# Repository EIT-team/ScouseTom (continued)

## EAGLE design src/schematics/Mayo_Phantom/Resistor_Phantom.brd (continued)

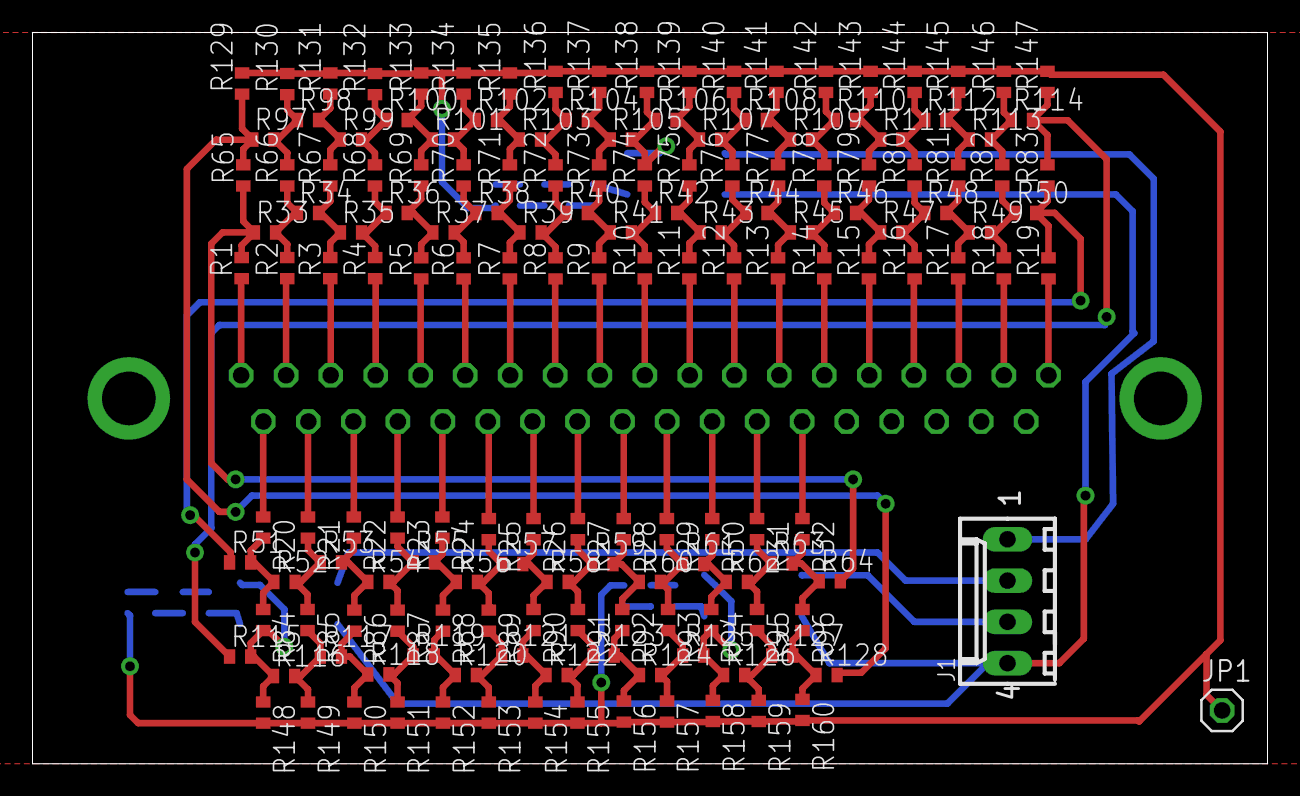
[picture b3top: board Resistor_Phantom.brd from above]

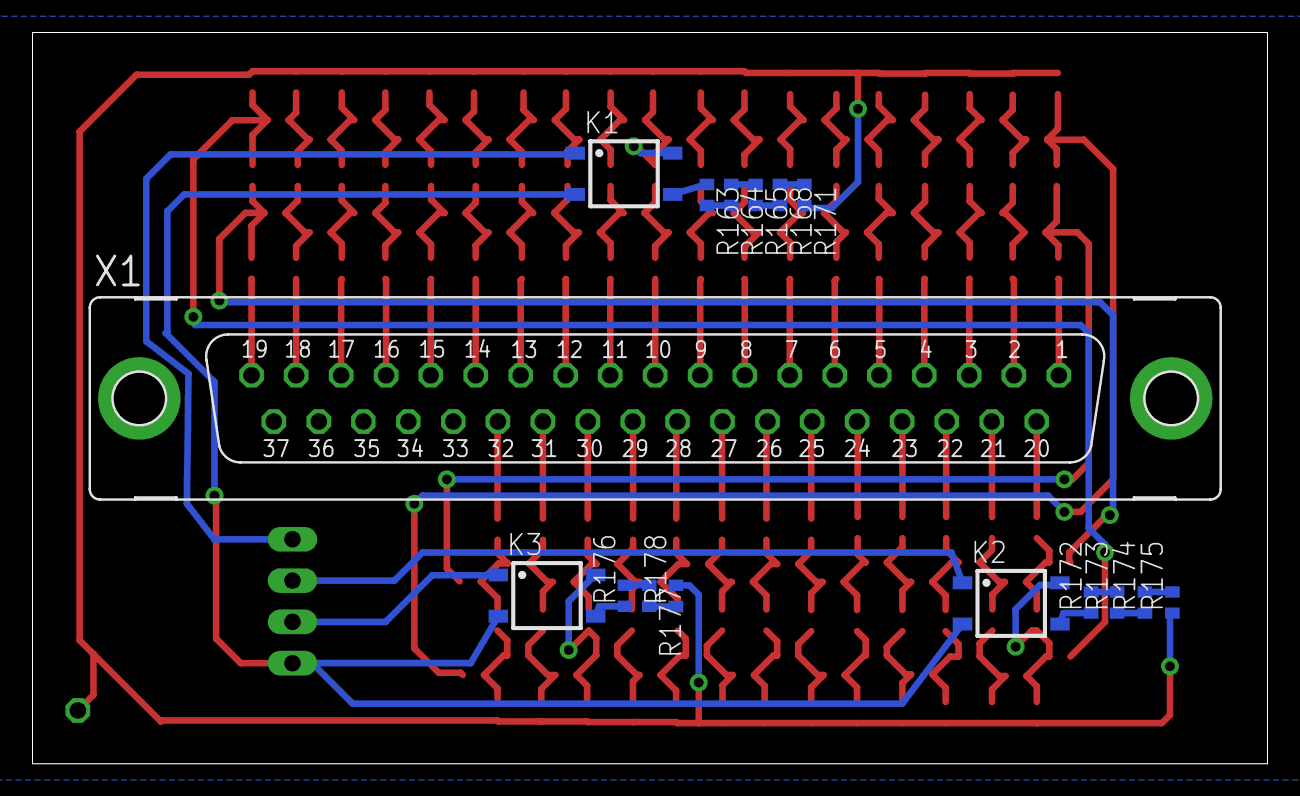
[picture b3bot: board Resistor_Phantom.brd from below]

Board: 2 copper layers, 76.0 x 45.0 mm, 178 parts (16 on the bottom side), 113 nets.

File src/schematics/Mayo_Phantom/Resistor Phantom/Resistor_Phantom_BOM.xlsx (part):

Part | Value | Device | Package | Description | MPN | OC_FARNELL | PCBTRAINFREE
K1 | AQY221R2S | AQY221R2S | SOP04 | PHOTOMOS Relay RF (Radio Frequency) NAiS | AQY221R2S | 1653770
K2 | AQY221R2S | AQY221R2S | SOP04 | PHOTOMOS Relay RF (Radio Frequency) NAiS | AQY221R2S | 1653770
K3 | AQY221R2S | AQY221R2S | SOP04 | PHOTOMOS Relay RF (Radio Frequency) NAiS | AQY221R2S | 1653770
R1 | 1k | R-EU_R0402 | R0402 | RESISTOR, European symbol | MC00625W040211K | 1358043 | PCBTRAINFREESTOCK
R2 | 1k | R-EU_R0402 | R0402 | RESISTOR, European symbol | MC00625W040211K | 1358043 | PCBTRAINFREESTOCK
R3 | 1k | R-EU_R0402 | R0402 | RESISTOR, European symbol | MC00625W040211K | 1358043 | PCBTRAINFREESTOCK
R4 | 1k | R-EU_R0402 | R0402 | RESISTOR, European symbol | MC00625W040211K | 1358043 | PCBTRAINFREESTOCK
R5 | 1k | R-EU_R0402 | R0402 | RESISTOR, European symbol | MC00625W040211K | 1358043 | PCBTRAINFREESTOCK
R6 | 1k | R-EU_R0402 | R0402 | RESISTOR, European symbol | MC00625W040211K | 1358043 | PCBTRAINFREESTOCK
R7 | 1k | R-EU_R0402 | R0402 | RESISTOR, European symbol | MC00625W040211K | 1358043 | PCBTRAINFREESTOCK
R8 | 1k | R-EU_R0402 | R0402 | RESISTOR, European symbol | MC00625W040211K | 1358043 | PCBTRAINFREESTOCK
R9 | 1k | R-EU_R0402 | R0402 | RESISTOR, European symbol | MC00625W040211K | 1358043 | PCBTRAINFREESTOCK
R10 | 1k | R-EU_R0402 | R0402 | RESISTOR, European symbol | MC00625W040211K | 1358043 | PCBTRAINFREESTOCK
R11 | 1k | R-EU_R0402 | R0402 | RESISTOR, European symbol | MC00625W040211K | 1358043 | PCBTRAINFREESTOCK
R12 | 1k | R-EU_R0402 | R0402 | RESISTOR, European symbol | MC00625W040211K | 1358043 | PCBTRAINFREESTOCK
R13 | 1k | R-EU_R0402 | R0402 | RESISTOR, European symbol | MC00625W040211K | 1358043 | PCBTRAINFREESTOCK
R14 | 1k | R-EU_R0402 | R0402 | RESISTOR, European symbol | MC00625W040211K | 1358043 | PCBTRAINFREESTOCK
R15 | 1k | R-EU_R0402 | R0402 | RESISTOR, European symbol | MC00625W040211K | 1358043 | PCBTRAINFREESTOCK
R16 | 1k | R-EU_R0402 | R0402 | RESISTOR, European symbol | MC00625W040211K | 1358043 | PCBTRAINFREESTOCK
R17 | 1k | R-EU_R0402 | R0402 | RESISTOR, European symbol | MC00625W040211K | 1358043 | PCBTRAINFREESTOCK
R18 | 1k | R-EU_R0402 | R0402 | RESISTOR, European symbol | MC00625W040211K | 1358043 | PCBTRAINFREESTOCK
R19 | 1k | R-EU_R0402 | R0402 | RESISTOR, European symbol | MC00625W040211K | 1358043 | PCBTRAINFREESTOCK
R20 | 1k | R-EU_R0402 | R0402 | RESISTOR, European symbol | MC00625W040211K | 1358043 | PCBTRAINFREESTOCK
R21 | 1k | R-EU_R0402 | R0402 | RESISTOR, European symbol | MC00625W040211K | 1358043 | PCBTRAINFREESTOCK
R22 | 1k | R-EU_R0402 | R0402 | RESISTOR, European symbol | MC00625W040211K | 1358043 | PCBTRAINFREESTOCK
R23 | 1k | R-EU_R0402 | R0402 | RESISTOR, European symbol | MC00625W040211K | 1358043 | PCBTRAINFREESTOCK
R24 | 1k | R-EU_R0402 | R0402 | RESISTOR, European symbol | MC00625W040211K | 1358043 | PCBTRAINFREESTOCK
R25 | 1k | R-EU_R0402 | R0402 | RESISTOR, European symbol | MC00625W040211K | 1358043 | PCBTRAINFREESTOCK
R26 | 1k | R-EU_R0402 | R0402 | RESISTOR, European symbol | MC00625W040211K | 1358043 | PCBTRAINFREESTOCK
R27 | 1k | R-EU_R0402 | R0402 | RESISTOR, European symbol | MC00625W040211K | 1358043 | PCBTRAINFREESTOCK
R28 | 1k | R-EU_R0402 | R0402 | RESISTOR, European symbol | MC00625W040211K | 1358043 | PCBTRAINFREESTOCK
R29 | 1k | R-EU_R0402 | R0402 | RESISTOR, European symbol | MC00625W040211K | 1358043 | PCBTRAINFREESTOCK
R30 | 1k | R-EU_R0402 | R0402 | RESISTOR, European symbol | MC00625W040211K | 1358043 | PCBTRAINFREESTOCK
R31 | 1k | R-EU_R0402 | R0402 | RESISTOR, European symbol | MC00625W040211K | 1358043 | PCBTRAINFREESTOCK
R32 | 1k | R-EU_R0402 | R0402 | RESISTOR, European symbol | MC00625W040211K | 1358043 | PCBTRAINFREESTOCK
R33 | 1k | R-EU_R0402 | R0402 | RESISTOR, European symbol | MC00625W040211K | 1358043 | PCBTRAINFREESTOCK
R34 | 1k | R-EU_R0402 | R0402 | RESISTOR, European symbol | MC00625W040211K | 1358043 | PCBTRAINFREESTOCK
R35 | 1k | R-EU_R0402 | R0402 | RESISTOR, European symbol | MC00625W040211K | 1358043 | PCBTRAINFREESTOCK
R36 | 1k | R-EU_R0402 | R0402 | RESISTOR, European symbol | MC00625W040211K | 1358043 | PCBTRAINFREESTOCK
R37 | 1k | R-EU_R0402 | R0402 | RESISTOR, European symbol | MC00625W040211K | 1358043 | PCBTRAINFREESTOCK
R38 | 1k | R-EU_R0402 | R0402 | RESISTOR, European symbol | MC00625W040211K | 1358043 | PCBTRAINFREESTOCK
R39 | 1k | R-EU_R0402 | R0402 | RESISTOR, European symbol | MC00625W040211K | 1358043 | PCBTRAINFREESTOCK
R40 | 1k | R-EU_R0402 | R0402 | RESISTOR, European symbol | MC00625W040211K | 1358043 | PCBTRAINFREESTOCK
R41 | 1k | R-EU_R0402 | R0402 | RESISTOR, European symbol | MC00625W040211K | 1358043 | PCBTRAINFREESTOCK
R42 | 1k | R-EU_R0402 | R0402 | RESISTOR, European symbol | MC00625W040211K | 1358043 | PCBTRAINFREESTOCK
R43 | 1k | R-EU_R0402 | R0402 | RESISTOR, European symbol | MC00625W040211K | 1358043 | PCBTRAINFREESTOCK
R44 | 1k | R-EU_R0402 | R0402 | RESISTOR, European symbol | MC00625W040211K | 1358043 | PCBTRAINFREESTOCK
R45 | 1k | R-EU_R0402 | R0402 | RESISTOR, European symbol | MC00625W040211K | 1358043 | PCBTRAINFREESTOCK
R46 | 1k | R-EU_R0402 | R0402 | RESISTOR, European symbol | MC00625W040211K | 1358043 | PCBTRAINFREESTOCK
R47 | 1k | R-EU_R0402 | R0402 | RESISTOR, European symbol | MC00625W040211K | 1358043 | PCBTRAINFREESTOCK
R48 | 1k | R-EU_R0402 | R0402 | RESISTOR, European symbol | MC00625W040211K | 1358043 | PCBTRAINFREESTOCK
R49 | 1k | R-EU_R0402 | R0402 | RESISTOR, European symbol | MC00625W040211K | 1358043 | PCBTRAINFREESTOCK
R50 | 1k | R-EU_R0402 | R0402 | RESISTOR, European symbol | MC00625W040211K | 1358043 | PCBTRAINFREESTOCK
R51 | 1k | R-EU_R0402 | R0402 | RESISTOR, European symbol | MC00625W040211K | 1358043 | PCBTRAINFREESTOCK
R52 | 1k | R-EU_R0402 | R0402 | RESISTOR, European symbol | MC00625W040211K | 1358043 | PCBTRAINFREESTOCK
R53 | 1k | R-EU_R0402 | R0402 | RESISTOR, European symbol | MC00625W040211K | 1358043 | PCBTRAINFREESTOCK
R54 | 1k | R-EU_R0402 | R0402 | RESISTOR, European symbol | MC00625W040211K | 1358043 | PCBTRAINFREESTOCK
R55 | 1k | R-EU_R0402 | R0402 | RESISTOR, European symbol | MC00625W040211K | 1358043 | PCBTRAINFREESTOCK
R56 | 1k | R-EU_R0402 | R0402 | RESISTOR, European symbol | MC00625W040211K | 1358043 | PCBTRAINFREESTOCK
R57 | 1k | R-EU_R0402 | R0402 | RESISTOR, European symbol | MC00625W040211K | 1358043 | PCBTRAINFREESTOCK
R58 | 1k | R-EU_R0402 | R0402 | RESISTOR, European symbol | MC00625W040211K | 1358043 | PCBTRAINFREESTOCK
R59 | 1k | R-EU_R0402 | R0402 | RESISTOR, European symbol | MC00625W040211K | 1358043 | PCBTRAINFREESTOCK
R60 | 1k | R-EU_R0402 | R0402 | RESISTOR, European symbol | MC00625W040211K | 1358043 | PCBTRAINFREESTOCK
R61 | 1k | R-EU_R0402 | R0402 | RESISTOR, European symbol | MC00625W040211K | 1358043 | PCBTRAINFREESTOCK
R62 | 1k | R-EU_R0402 | R0402 | RESISTOR, European symbol | MC00625W040211K | 1358043 | PCBTRAINFREESTOCK
R63 | 1k | R-EU_R0402 | R0402 | RESISTOR, European symbol | MC00625W040211K | 1358043 | PCBTRAINFREESTOCK
R64 | 1k | R-EU_R0402 | R0402 | RESISTOR, European symbol | MC00625W040211K | 1358043 | PCBTRAINFREESTOCK
R65 | 3k | R-EU_R0402 | R0402 | RESISTOR, European symbol | MC00625W040213K | 2130389 | PCBTRAINFREESTOCK
R66 | 3k | R-EU_R0402 | R0402 | RESISTOR, European symbol | MC00625W040213K | 2130389 | PCBTRAINFREESTOCK
R67 | 3k | R-EU_R0402 | R0402 | RESISTOR, European symbol | MC00625W040213K | 2130389 | PCBTRAINFREESTOCK
R68 | 3k | R-EU_R0402 | R0402 | RESISTOR, European symbol | MC00625W040213K | 2130389 | PCBTRAINFREESTOCK
R69 | 3k | R-EU_R0402 | R0402 | RESISTOR, European symbol | MC00625W040213K | 2130389 | PCBTRAINFREESTOCK
R70 | 3k | R-EU_R0402 | R0402 | RESISTOR, European symbol | MC00625W040213K | 2130389 | PCBTRAINFREESTOCK
R71 | 3k | R-EU_R0402 | R0402 | RESISTOR, European symbol | MC00625W040213K | 2130389 | PCBTRAINFREESTOCK
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
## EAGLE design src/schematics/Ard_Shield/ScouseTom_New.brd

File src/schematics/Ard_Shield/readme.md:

# Arduino Shield

The Arduino Shield has several functions:

- Communication with PC via USB serial. This is done through the programming port on the Arduinio Due. i.e. `Serial.print` etc. with baud rate 115200
- Communication with Keithley 6221 current source via isolated RS232 port - baud rate 57600 via Serial port `Serial1.print` etc.
- Reference triggers to EEG system. Pulses sent to digital inputs of EEG systems, isolated from Arduino pins
- Control of switch networks. Control signals sent to Switchboard (isolation on the switchboard)
- Stimulation triggers - Based on phase marker of Keithley 6221 - stimulation pulses are randomised with respect to the phase of the injected current.
- Stimulation voltage - the voltage of the pulses can be sent from 3.3 to 12 V. This is useful for controlling the electrical stimulator box

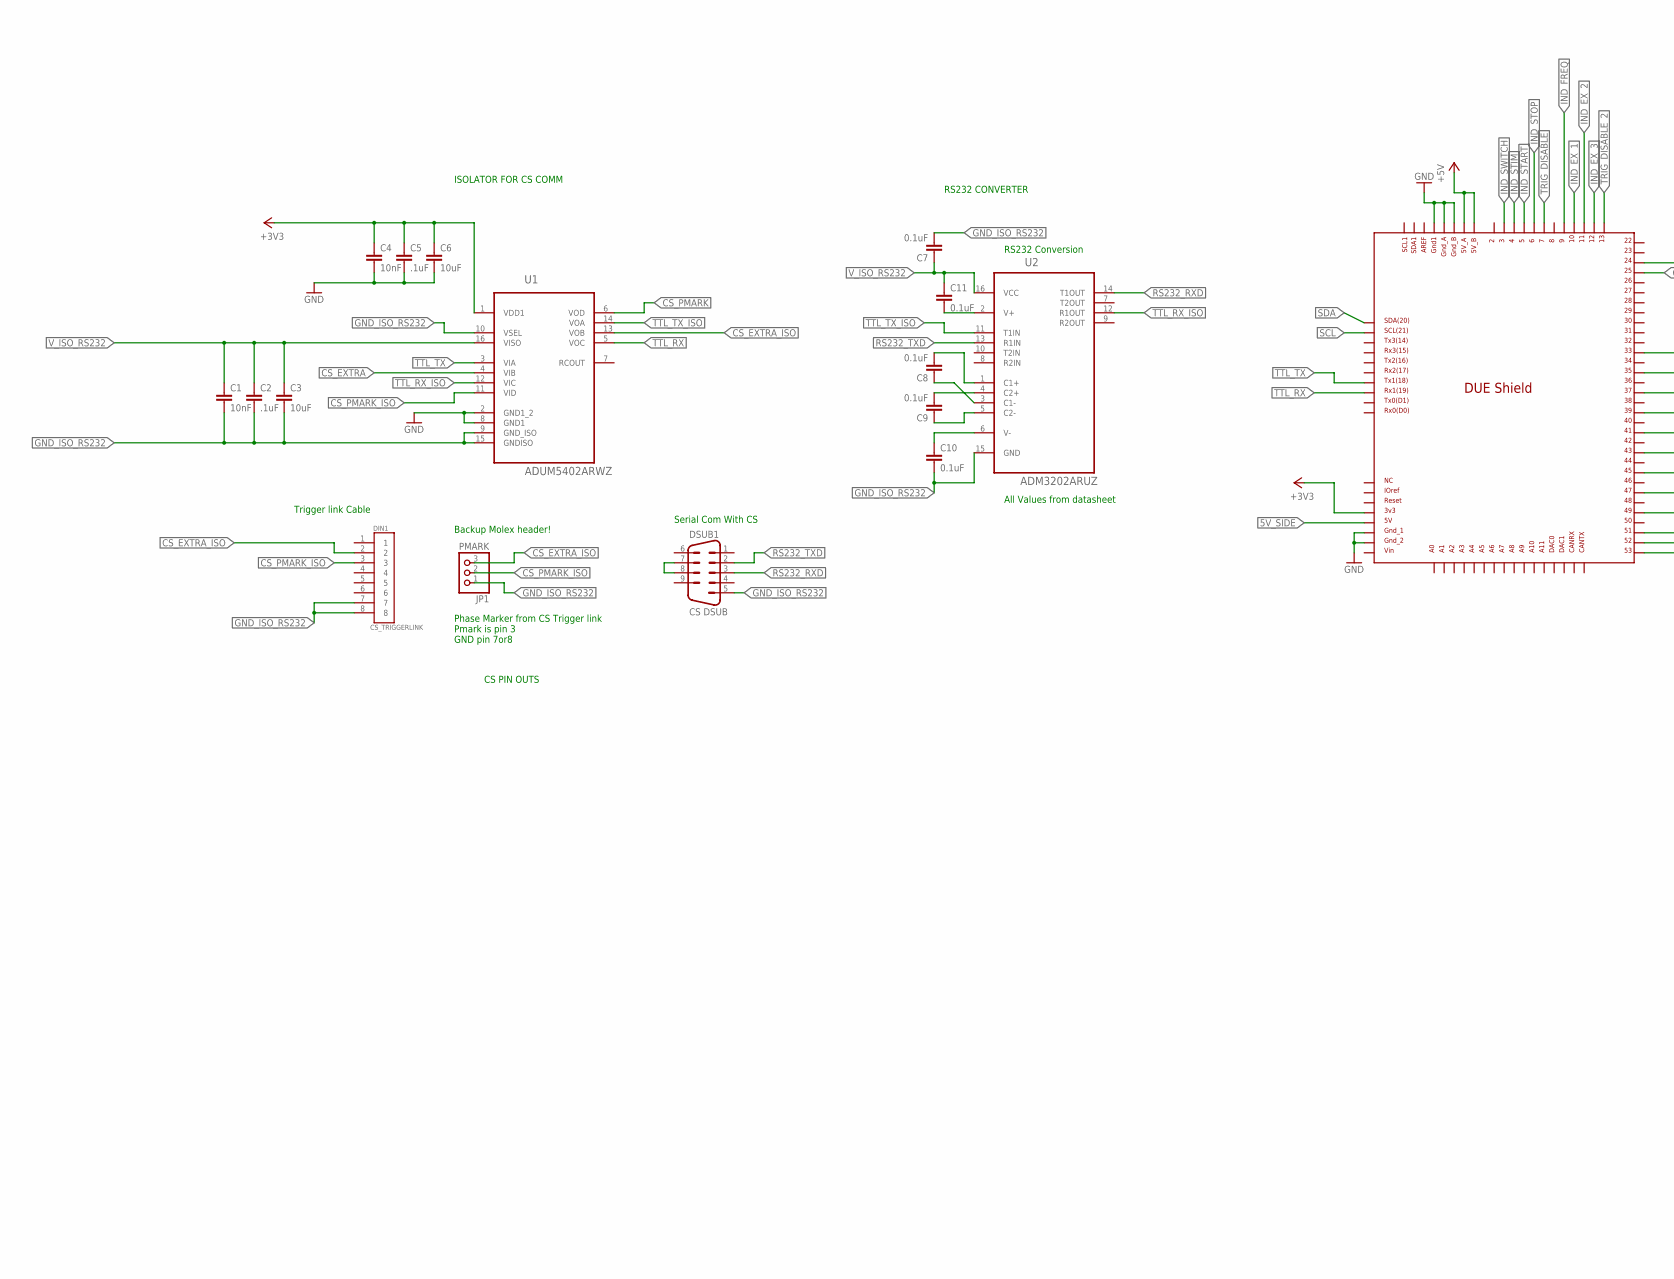
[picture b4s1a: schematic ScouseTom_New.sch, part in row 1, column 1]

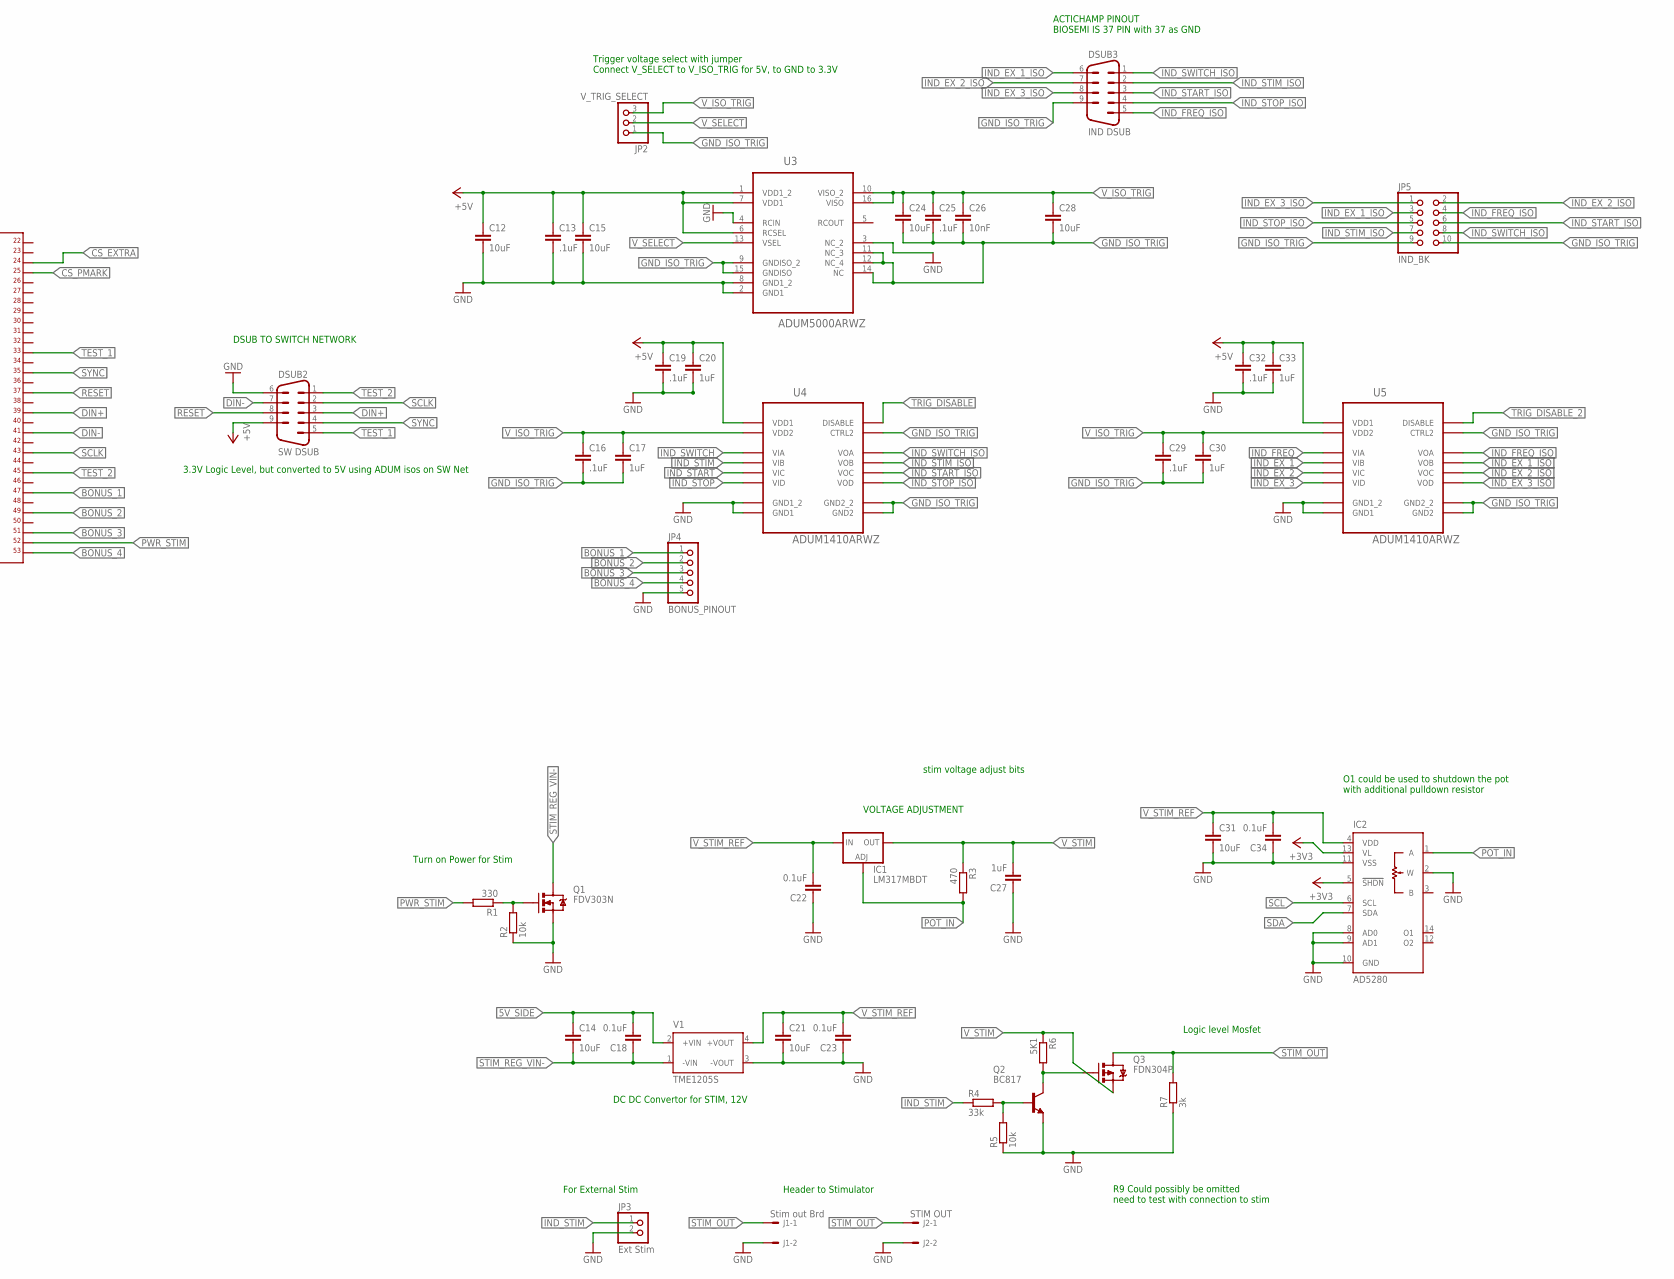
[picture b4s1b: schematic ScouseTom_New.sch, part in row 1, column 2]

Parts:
ARD1: DUE(NOMID)
C1, C4, C26: 10nF; C0805
C2, C5, C13, C16, C19, C25, C29, C32: .1uF; C0805
C3, C6, C12, C14, C15, C21, C24, C28, C31: 10uF; C0805
C7, C8, C9, C10, C11, C18, C22, C23, C34: 0.1uF; C0805
C17, C20, C27, C30, C33: 1uF; C0805
DIN1: CS_TRIGGERLINK; DIN8
DSUB1: CS DSUB; DSUB9
DSUB2: SW DSUB; DSUB9
DSUB3: IND DSUB; DSUB9
IC1: LM317MBDT; DPACK
IC2: AD5280; TSSOP14
J1: Stim out Brd; 6410-02
J2: STIM OUT; 7395-02
JP1: PMARK; 1X03
JP2: V_TRIG_SELECT; 1X03
JP3: Ext Stim; 1X02
JP4: BONUS_PINOUT; 1X05
JP5: IND_BK; 2X05
Q1: FDV303N; SOT323
Q2: BC817; SOT23-BEC
Q3: FDN304P; SOT23-3
R1: 330; R0805
R2, R5: 10k; R0805
R3: 470; R0805
R4: 33k; R0805
R6: 5K1; R0805
R7: 3k; R0805
U1: ADUM5402ARWZ; SOIC127P1032X265-16N
U2: ADM3202ARUZ; SOP65P640X120-16N
U3: ADUM5000ARWZ; SOIC127P1032X265-16N
U4, U5: ADUM1410ARWZ; SOIC127P1032X265-16N
V1: TME1205S; TME

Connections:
5V_SIDE: ARD1.5V, C14.1, C18.2, V1.2 (+VIN)
+3V3: ARD1.3V3, C4.1, C5.1, C6.1, IC2.5 (!SHDN), IC2.13 (VL), U1.1 (VDD1)
+5V: ARD1.5V_A, ARD1.5V_B, C12.1, C13.1, C15.1, C19.1, C20.1, C32.1, C33.1, DSUB2.9, U3.1 (VDD1_2), U3.6 (RCSEL), U3.7 (VDD1), U4.1 (VDD1), U5.1 (VDD1)
BONUS_1: ARD1.47, JP4.1
BONUS_2: ARD1.49, JP4.2
BONUS_3: ARD1.51, JP4.3
BONUS_4: ARD1.53, JP4.4
CS_EXTRA: ARD1.24, U1.4 (VIB)
CS_EXTRA_ISO: DIN1.2, JP1.3, U1.13 (VOB); also elsewhere on the board
CS_PMARK: ARD1.25, U1.6 (VOD)
CS_PMARK_ISO: DIN1.3, JP1.2, U1.11 (VID); also elsewhere on the board
DIN+: ARD1.39, DSUB2.3
DIN-: ARD1.41, DSUB2.7
GND: ARD1.GND1, ARD1.GND_1, ARD1.GND_2, ARD1.GND_A, ARD1.GND_B, C4.2, C5.2, C6.2, C12.2, C13.2, C15.2, C19.2, C20.2, C21.2, C22.1, C23.1, C27.1, C31.2, C32.2, C33.2, C34.1, DSUB2.6, IC2.2 (W), IC2.8 (AD0), IC2.9 (AD1), IC2.10 (GND), IC2.11 (VSS), J1.2, J2.2, JP3.2, JP4.5, Q1.2 (S), Q2.E, R2.1, R5.1, R7.1, U1.2 (GND1_2), U1.8 (GND1), U3.2 (GND1), U3.3 (NC_2), U3.4 (RCIN), U3.8 (GND1_2), U4.2 (GND1_2), U4.8 (GND1), U5.2 (GND1_2), U5.8 (GND1), V1.3 (-VOUT); also elsewhere on the board
GND_ISO_RS232: C1.2, C2.2, C3.2, C7.2, C10.2, DIN1.7, DIN1.8, DSUB1.5, JP1.1, U1.9 (GND_ISO), U1.10 (VSEL), U1.15 (GNDISO), U2.15 (GND); also elsewhere on the board
GND_ISO_TRIG: C16.2, C17.2, C24.2, C25.2, C26.2, C28.2, C29.2, C30.2, DSUB3.9, JP2.1, JP5.9, JP5.10, U3.9 (GNDISO_2), U3.11 (NC_3), U3.12 (NC_4), U3.14 (NC), U3.15 (GNDISO), U4.9 (GND2_2), U4.10 (CTRL2), U4.15 (GND2), U5.9 (GND2_2), U5.10 (CTRL2), U5.15 (GND2)
IND_EX_1: ARD1.10, U5.4 (VIB)
IND_EX_1_ISO: DSUB3.6, JP5.3, U5.13 (VOB)
IND_EX_2: ARD1.11, U5.5 (VIC)
IND_EX_2_ISO: DSUB3.7, JP5.2, U5.12 (VOC)
IND_EX_3: ARD1.12, U5.6 (VID)
IND_EX_3_ISO: DSUB3.8, JP5.1, U5.11 (VOD)
IND_FREQ: ARD1.9, U5.3 (VIA)
IND_FREQ_ISO: DSUB3.5, JP5.4, U5.14 (VOA)
IND_START: ARD1.5, U4.5 (VIC)
IND_START_ISO: DSUB3.3, JP5.6, U4.12 (VOC)
IND_STIM: ARD1.4, JP3.1, R4.1, U4.4 (VIB)
IND_STIM_ISO: DSUB3.2, JP5.7, U4.13 (VOB)
IND_STOP: ARD1.6, U4.6 (VID)
IND_STOP_ISO: DSUB3.4, JP5.5, U4.11 (VOD)
IND_SWITCH: ARD1.3, U4.3 (VIA)
IND_SWITCH_ISO: DSUB3.1, JP5.8, U4.14 (VOA)
unnamed: Q2.B, R4.2, R5.2
unnamed: Q2.C, Q3.1 (G), R6.2
unnamed: DSUB1.7, DSUB1.8
unnamed: Q1.1 (G), R1.1, R2.2
unnamed: C8.2, U2.1 (C1+)
unnamed: C8.1, U2.3 (C1-)
unnamed: C9.2, U2.4 (C2+)
unnamed: C9.1, U2.5 (C2-)
unnamed: C11.2, U2.2 (V+)
unnamed: C10.1, U2.6 (V-)
POT_IN: IC1.1 (ADJ), IC2.1 (A), R3.2
PWR_STIM: ARD1.52, R1.2
RESET: ARD1.37, DSUB2.8
RS232_RXD: DSUB1.3, U2.14 (T1OUT)
RS232_TXD: DSUB1.2, U2.13 (R1IN)
SCL: ARD1.SCL, IC2.6 (SCL)
SCLK: ARD1.43, DSUB2.2
SDA: ARD1.SDA, IC2.7 (SDA)
STIM_OUT: J1.1, J2.1, Q3.3 (D), R7.2
STIM_REG_VIN-: C14.2, C18.1, Q1.3 (D), V1.1 (-VIN)
SYNC: ARD1.35, DSUB2.4
TEST_1: ARD1.33, DSUB2.5; also elsewhere on the board
TEST_2: ARD1.45, DSUB2.1; also elsewhere on the board
TRIG_DISABLE: ARD1.7, U4.7 (DISABLE)
TRIG_DISABLE_2: ARD1.13, U5.7 (DISABLE)
TTL_RX: ARD1.RX1, U1.5 (VOC)
TTL_RX_ISO: U1.12 (VIC), U2.12 (R1OUT)
TTL_TX: ARD1.TX1, U1.3 (VIA)
TTL_TX_ISO: U1.14 (VOA), U2.11 (T1IN)
V_ISO_RS232: C1.1, C2.1, C3.1, C7.1, C11.1, U1.16 (VISO), U2.16 (VCC)
V_ISO_TRIG: C16.1, C17.1, C24.1, C25.1, C26.1, C28.1, C29.1, C30.1, JP2.3, U3.10 (VISO_2), U3.16 (VISO), U4.16 (VDD2), U5.16 (VDD2)
V_SELECT: JP2.2, U3.13 (VSEL)
V_STIM: C27.2, IC1.4 (OUT), Q3.2 (S), R3.1, R6.1
V_STIM_REF: C21.1, C22.2, C23.2, C31.1, C34.2, IC1.3 (IN), IC2.4 (VDD), V1.4 (+VOUT)

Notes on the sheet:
stim voltage adjust bits
RS232 Conversion
Phase Marker from CS Trigger link Pmark is pin 3 GND pin 7or8
Header to Stimulator
Logic level Mosfet
For External Stim
R9 Could possibly be omitted need to test with connection to stim
O1 could be used to shutdown the pot with additional pulldown resistor
Backup Molex header!
ACTICHAMP PINOUT BIOSEMI IS 37 PIN with 37 as GND
Trigger voltage select with jumper Connect V_SELECT to V_ISO_TRIG for 5V, to GND to 3.3V
DSUB TO SWITCH NETWORK
3.3V Logic Level, but converted to 5V using ADUM isos on SW Net
ISOLATOR FOR CS COMM
RS232 CONVERTER
CS PIN OUTS
Turn on Power for Stim
DC DC Convertor for STIM, 12V
VOLTAGE ADJUSTMENT
Trigger link Cable
Serial Com With CS
All Values from datasheet

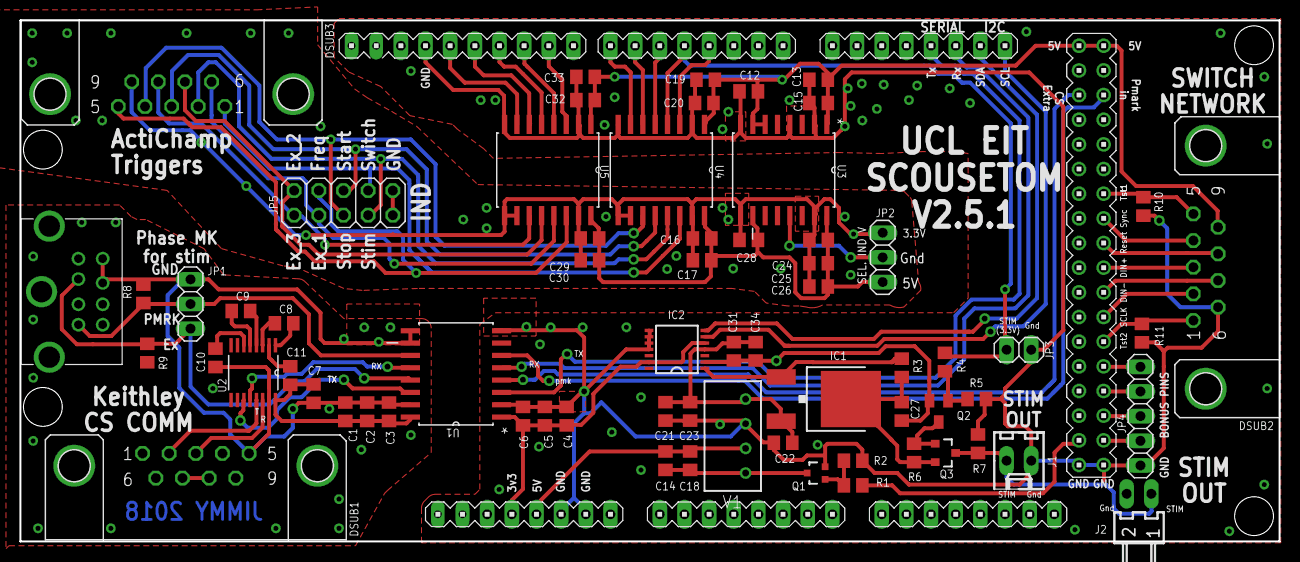
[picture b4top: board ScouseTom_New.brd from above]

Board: 2 copper layers, 129.7 x 53.7 mm, 68 parts (0 on the bottom side), 66 nets.

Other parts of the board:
R8, R9, R10, R11: 10k; R0805

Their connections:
CS_EXTRA_ISO: R9.1; also elsewhere on the board
CS_PMARK_ISO: R8.2; also elsewhere on the board
GND: R10.1, R11.1; also elsewhere on the board
GND_ISO_RS232: R8.1, R9.2; also elsewhere on the board
TEST_1: R10.2; also elsewhere on the board
TEST_2: R11.2; also elsewhere on the board

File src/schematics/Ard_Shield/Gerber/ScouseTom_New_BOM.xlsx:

Part | Value | Device | Package | Description | MPN | OC_FARNELL | PCB TRAIN FREE | unique | non free stock to purchase
C1 | 10nF | C-EUC0805 | C0805 | CAPACITOR, European symbol | MC0805B103K500CT | 1759246 | PCB Train Free Component Stock | 1759246 | 0
C2 | 0.1uF | C-EUC0805 | C0805 | CAPACITOR, European symbol | MC0805B104K500CT | 1759265 | PCB Train Free Component Stock | 1759265 | 0
C3 | 10uF | C-EUC0805 | C0805 | CAPACITOR, European symbol | MC0805X106K6R3CT | 2320852 |  | 2320852 | 9
C4 | 10nF | C-EUC0805 | C0805 | CAPACITOR, European symbol | MC0805B103K500CT | 1759246 | PCB Train Free Component Stock | 2320827 | 0
C5 | 0.1uF | C-EUC0805 | C0805 | CAPACITOR, European symbol | MC0805B104K500CT | 1759265 | PCB Train Free Component Stock | 2102587 | 0
C6 | 10uF | C-EUC0805 | C0805 | CAPACITOR, European symbol | MC0805X106K6R3CT | 2320852 |  | 1438441 | 1
C7 | 0.1uF | C-EUC0805 | C0805 | CAPACITOR, European symbol | MC0805B104K500CT | 1759265 | PCB Train Free Component Stock | 2336831 | 0
C8 | 0.1uF | C-EUC0805 | C0805 | CAPACITOR, European symbol | MC0805B104K500CT | 1759265 | PCB Train Free Component Stock | 2336780 | 0
C9 | 0.1uF | C-EUC0805 | C0805 | CAPACITOR, European symbol | MC0805B104K500CT | 1759265 | PCB Train Free Component Stock | 2352451 | 0
C10 | 0.1uF | C-EUC0805 | C0805 | CAPACITOR, European symbol | MC0805B104K500CT | 1759265 | PCB Train Free Component Stock | 2129074 | 0
C11 | 0.1uF | C-EUC0805 | C0805 | CAPACITOR, European symbol | MC0805B104K500CT | 1759265 | PCB Train Free Component Stock | 9332391 | 0
C12 | 10uF | C-EUC0805 | C0805 | CAPACITOR, European symbol | MC0805X106K6R3CT | 2320852 |  | 2129087 | 0
C13 | 0.1uF | C-EUC0805 | C0805 | CAPACITOR, European symbol | MC0805B104K500CT | 1759265 | PCB Train Free Component Stock | 2129237 | 0
C14 | 10uF | C-EUC0805 | C0805 | CAPACITOR, European symbol | MC0805X106K6R3CT | 2320852 |  | 2129171 | 0
C15 | 10uF | C-EUC0805 | C0805 | CAPACITOR, European symbol | MC0805X106K6R3CT | 2320852 |  | 2129150 | 0
C16 | 0.1uF | C-EUC0805 | C0805 | CAPACITOR, European symbol | MC0805B104K500CT | 1759265 | PCB Train Free Component Stock | 1838922 | 1
C17 | 1uF | C-EUC0805 | C0805 | CAPACITOR, European symbol | MC0805B105K250CT | 2320827 | PCB Train Free Component Stock | 9425586 | 1
C18 | 0.1uF | C-EUC0805 | C0805 | CAPACITOR, European symbol | MC0805B104K500CT | 1759265 | PCB Train Free Component Stock | 2102522 | 1
C19 | 0.1uF | C-EUC0805 | C0805 | CAPACITOR, European symbol | MC0805B104K500CT | 1759265 | PCB Train Free Component Stock | 2067770 | 2
C20 | 1uF | C-EUC0805 | C0805 | CAPACITOR, European symbol | MC0805B105K250CT | 2320827 | PCB Train Free Component Stock | #N/A | 0
C21 | 10uF | C-EUC0805 | C0805 | CAPACITOR, European symbol | MC0805X106K6R3CT | 2320852 |  | #N/A | 0
C22 | 0.1uF | C-EUC0805 | C0805 | CAPACITOR, European symbol | MC0805B104K500CT | 1759265 | PCB Train Free Component Stock | #N/A | 0
C23 | 0.1uF | C-EUC0805 | C0805 | CAPACITOR, European symbol | MC0805B104K500CT | 1759265 | PCB Train Free Component Stock | #N/A | 0
C24 | 10uF | C-EUC0805 | C0805 | CAPACITOR, European symbol | MC0805X106K6R3CT | 2320852 |  | #N/A | 0
C25 | 0.1uF | C-EUC0805 | C0805 | CAPACITOR, European symbol | MC0805B104K500CT | 1759265 | PCB Train Free Component Stock | #N/A | 0
C26 | 10nF | C-EUC0805 | C0805 | CAPACITOR, European symbol | MC0805B103K500CT | 1759246 | PCB Train Free Component Stock | #N/A | 0
C27 | 1uF | C-EUC0805 | C0805 | CAPACITOR, European symbol | MC0805B105K250CT | 2320827 | PCB Train Free Component Stock | #N/A | 0
C28 | 10uF | C-EUC0805 | C0805 | CAPACITOR, European symbol | MC0805X106K6R3CT | 2320852 |  | #N/A | 0
C29 | 0.1uF | C-EUC0805 | C0805 | CAPACITOR, European symbol | MC0805B104K500CT | 1759265 | PCB Train Free Component Stock | #N/A | 0
C30 | 1uF | C-EUC0805 | C0805 | CAPACITOR, European symbol | MC0805B105K250CT | 2320827 | PCB Train Free Component Stock | #N/A | 0
C31 | 10uF | C-EUC0805 | C0805 | CAPACITOR, European symbol | MC0805X106K6R3CT | 2320852 |  | #N/A | 0
C32 | 0.1uF | C-EUC0805 | C0805 | CAPACITOR, European symbol | MC0805B104K500CT | 1759265 | PCB Train Free Component Stock | #N/A | 0
C33 | 1uF | C-EUC0805 | C0805 | CAPACITOR, European symbol | MC0805B105K250CT | 2320827 | PCB Train Free Component Stock | #N/A | 0
C34 | 0.1uF | C-EUC0805 | C0805 | CAPACITOR, European symbol | MC0805B104K500CT | 1759265 | PCB Train Free Component Stock | #N/A | 0
IC1 | LM317MBDT | LM317MBDT | DPACK | 500 mA Adjustable Output Positive Voltage Regulator | LM317MDTX | 2102587 | PCB Train Free Component Stock | #N/A
IC2 | AD5280 | AD5280 | TSSOP14 | Single +15 V/±5 V, 256-Position, I2C-Compatible Digital Potentiometer | AD5280BRUZ20 | 1438441 |  | #N/A
Q1 | FDV303N | MOSFET-NCHANNEL2N7002PW | SOT323 | Common NMOSFET Parts | FDV303N | 2336831 | PCB Train Free Component Stock | #N/A
Q2 | BC817 | BC817-40SMD | SOT23-BEC | NPN Transistor | BC817-40,215 | 2336780 | PCB Train Free Component Stock | #N/A
Q3 | FDN304P | MOSFET-PCHANNEL | SOT23-3 | Generic PMOSFET | FDN304P | 2352451 | PCB Train Free Component Stock | #N/A
R1 | 330 | R-EU_R0805 | R0805 | RESISTOR, European symbol | MC01W08051330R | 2129074 | PCB Train Free Component Stock | #N/A
R2 | 10k | R-EU_R0805 | R0805 | RESISTOR, European symbol | MC01W0805110K | 9332391 | PCB Train Free Component Stock | #N/A
R3 | 470 | R-EU_R0805 | R0805 | RESISTOR, European symbol | MC01W08051470R | 2129087 | PCB Train Free Component Stock | #N/A
R4 | 33k | R-EU_R0805 | R0805 | RESISTOR, European symbol | MC01W0805133K | 2129237 | PCB Train Free Component Stock | #N/A
R5 | 10k | R-EU_R0805 | R0805 | RESISTOR, European symbol | MC01W0805110K | 9332391 | PCB Train Free Component Stock | #N/A
R6 | 5K1 | R-EU_R0805 | R0805 | RESISTOR, European symbol | MC01W080515K1 | 2129171 | PCB Train Free Component Stock | #N/A
R7 | 3k | R-EU_R0805 | R0805 | RESISTOR, European symbol | MC01W080513K | 2129150 | PCB Train Free Component Stock | #N/A
R8 | 10k | R-EU_R0805 | R0805 | RESISTOR, European symbol | MC01W0805110K | 9332391 | PCB Train Free Component Stock | #N/A
R9 | 10k | R-EU_R0805 | R0805 | RESISTOR, European symbol | MC01W0805110K | 9332391 | PCB Train Free Component Stock | #N/A
R10 | 10k | R-EU_R0805 | R0805 | RESISTOR, European symbol | MC01W0805110K | 9332391 | PCB Train Free Component Stock
R11 | 10k | R-EU_R0805 | R0805 | RESISTOR, European symbol | MC01W0805110K | 9332391 | PCB Train Free Component Stock
U1 | ADUM5402ARWZ | ADUM5402ARWZ | SOIC127P1032X265-16N | Quad-Channel Isolators with Integrated DC-to-DC Converter | ADUM5402ARWZ | 1838922 |  |  | 15
U2 | ADM3202ARUZ | ADM3202ARUZ | SOP65P640X120-16N | Low Power, 3.3 V, RS-232 Line Drivers/Receivers | ADM3202ARUZ | 9425586
U3 | ADUM5000ARWZ | ADUM5000ARWZ | SOIC127P1032X265-16N | 2.5 kV, Isolated DC-to-DC Converter | ADUM5000ARWZ | 2102522
U4 | ADUM1410ARWZ | ADUM1410ARWZ | SOIC127P1032X265-16N | ISOLATOR, DGTL, 4CHAN | ADUM1410ARWZ | 2067770
U5 | ADUM1410ARWZ | ADUM1410ARWZ | SOIC127P1032X265-16N | ISOLATOR, DGTL, 4CHAN | ADUM1410ARWZ | 2067770
 |  |  |  |  | Number unique components | 18.999999999999996
 |  |  |  |  | Number Free | 40
 |  |  |  |  | Number Non Free | 15
 |  |  |  |  | Total | 55

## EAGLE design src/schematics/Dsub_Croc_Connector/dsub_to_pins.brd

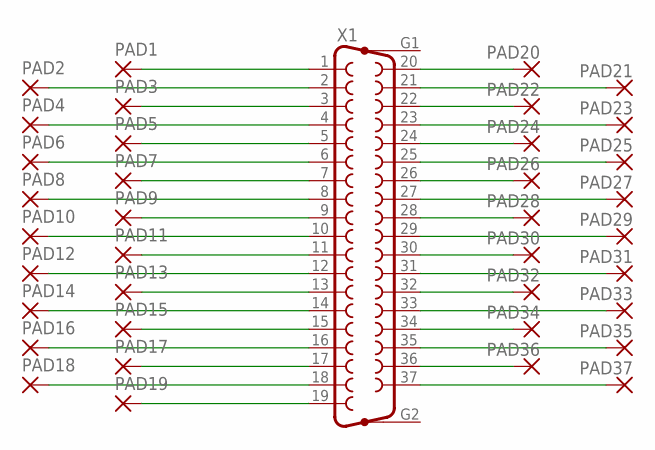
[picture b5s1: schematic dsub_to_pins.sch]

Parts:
PAD1, PAD2, PAD3, PAD4, PAD5, PAD6, PAD7, PAD8, PAD9, PAD10, PAD11, PAD12, PAD13, PAD14, PAD15, PAD16, PAD17, PAD18, PAD19, PAD20, PAD21, PAD22, PAD23, PAD24, PAD25, PAD26, PAD27, PAD28, PAD29, PAD30, PAD31, PAD32, PAD33, PAD34, PAD35, PAD36, PAD37: WIREPAD3,81/1,3; 3,81/1,3
X1: F37HP

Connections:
1: PAD1.1, X1.1
2: PAD2.1, X1.2
3: PAD3.1, X1.3
4: PAD4.1, X1.4
5: PAD5.1, X1.5
6: PAD6.1, X1.6
7: PAD7.1, X1.7
8: PAD8.1, X1.8
9: PAD9.1, X1.9
10: PAD10.1, X1.10
11: PAD11.1, X1.11
12: PAD12.1, X1.12
13: PAD13.1, X1.13
14: PAD14.1, X1.14
15: PAD15.1, X1.15
16: PAD16.1, X1.16
17: PAD17.1, X1.17
18: PAD18.1, X1.18
19: PAD19.1, X1.19
20: PAD20.1, X1.20
21: PAD21.1, X1.21
22: PAD22.1, X1.22
23: PAD23.1, X1.23
24: PAD24.1, X1.24
25: PAD25.1, X1.25
26: PAD26.1, X1.26
27: PAD27.1, X1.27
28: PAD28.1, X1.28
29: PAD29.1, X1.29
30: PAD30.1, X1.30
31: PAD31.1, X1.31
32: PAD32.1, X1.32
33: PAD33.1, X1.33
34: PAD34.1, X1.34
35: PAD35.1, X1.35
36: PAD36.1, X1.36
37: PAD37.1, X1.37

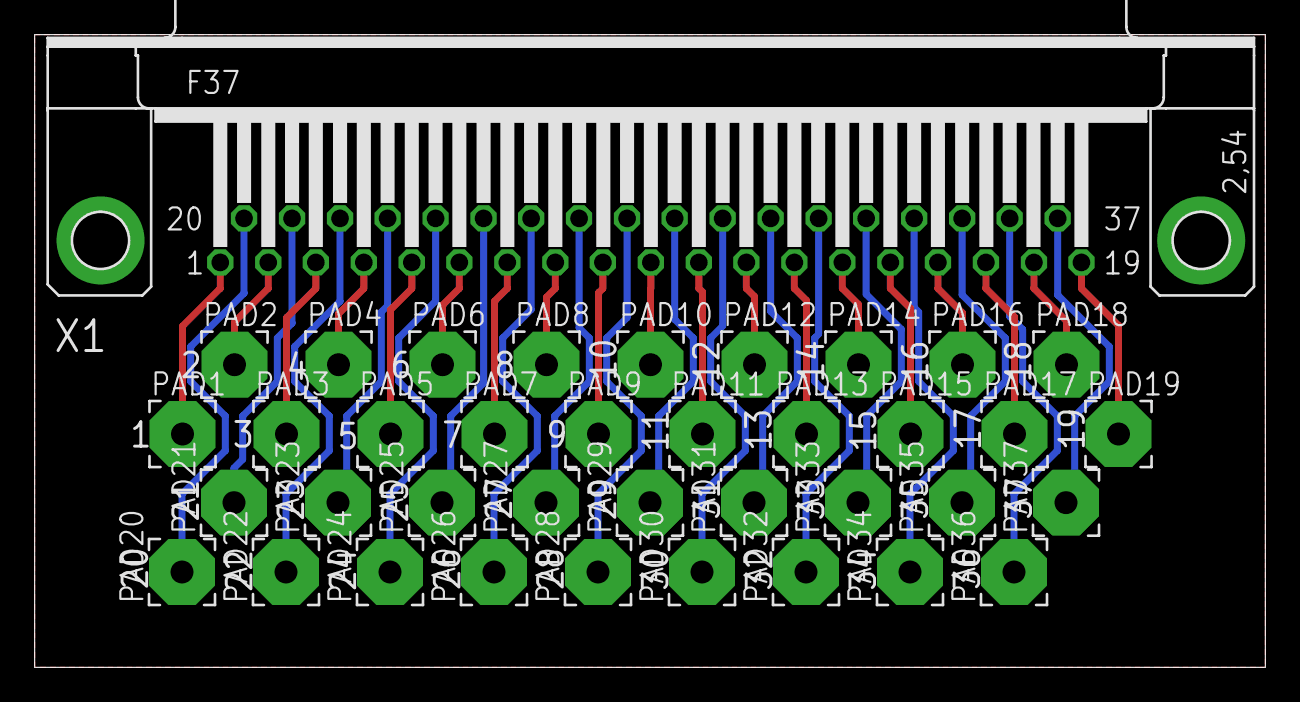
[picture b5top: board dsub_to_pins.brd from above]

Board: 2 copper layers, 71.0 x 36.5 mm, 38 parts (0 on the bottom side), 37 nets.
